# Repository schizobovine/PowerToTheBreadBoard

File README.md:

# PowerToTheBreadBoard
Variations of power supplies/regulators designed to be clamped on to a bread board.

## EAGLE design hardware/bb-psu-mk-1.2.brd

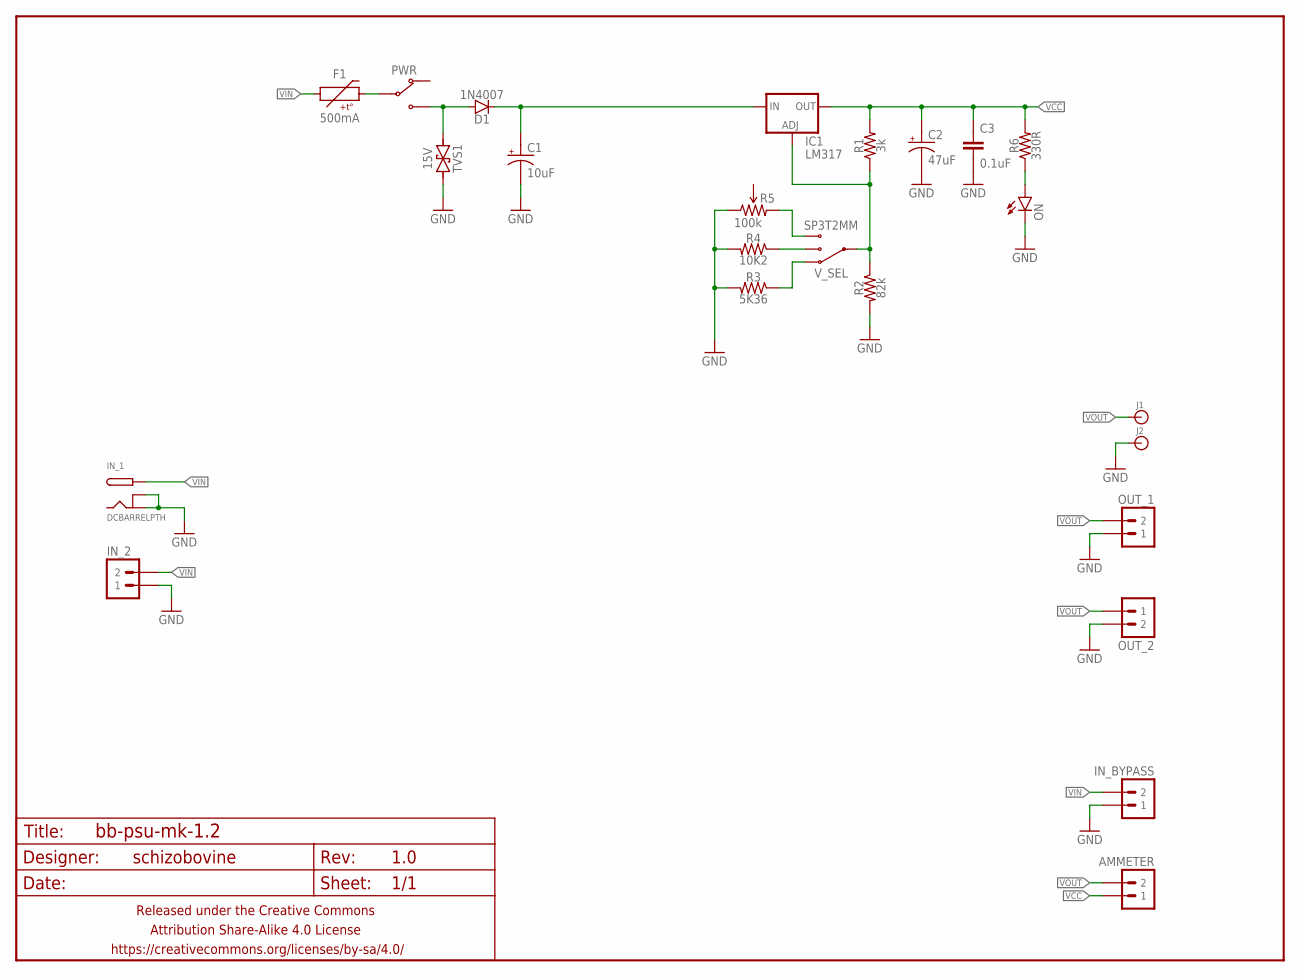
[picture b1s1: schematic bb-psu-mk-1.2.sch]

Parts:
AMMETER: M02PTH-CENTERED; 1X02-CENTER
C1: 10uF; E2,5-6
C2: 47uF; E2,5-6
C3: 0.1uF; C025-024X044
D1: 1N4007; DIODE-10.16MM
F1: 500mA; PTC-PTH-5.08MM
FRAME1: FRAME-LETTERNO_PACKAGE; DUMMY
IC1: LM317; TO220-THERMPAD
IN_1: DCBARRELPTH; DCJACK_2MM_PTH
IN_2: M02PTH-CENTERED-R+; 1X02-CENTER-R+
IN_BYPASS: M02PTH-CENTERED-R+; 1X02-CENTER-R+
J1, J2: BANANA_CONNPOAST; BINDING_POST
ON: LED3MM-LESS; LED3MM-LESSSILK
OUT_1: M02PTH-CENTERED-R+; 1X02-CENTER-R+
OUT_2: M023.5MM; SCREWTERMINAL-3.5MM-2
PWR: SWITCH-SPDTPTH-VERT-2.54MM; SWITCH-SPDT
R1: 3k; RESISTOR-AXIAL-PTH-7.62MM
R2: 82k; RESISTOR-AXIAL-PTH-7.62MM
R3: 5K36; RESISTOR-AXIAL-PTH-7.62MM
R4: 10K2; RESISTOR-AXIAL-PTH-7.62MM
R5: 100k; 3386U
R6: 330R; RESISTOR-AXIAL-PTH-6.35MM
TVS1: 15V; DO-41-TVS-BI-10.16MM
V_SEL: SP3T2MM; SP3T-2MM

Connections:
GND: C1.-, C2.-, C3.2, IN_1.BRK, IN_1.GND, IN_2.1, IN_BYPASS.1, J2.P$1, ON.K (C), OUT_1.1, OUT_2.2, R2.P$2 (2), R3.P$2 (2), R4.P$2 (2), R5.1 (CCW), TVS1.P$2 (2)
unnamed: D1.A, PWR.3 (NO), TVS1.P$1 (1)
unnamed: C1.+, D1.C, IC1.3 (IN)
unnamed: F1.P$2 (2), PWR.2 (COM)
unnamed: ON.A, R6.P$1 (1)
unnamed: R4.P$1 (1), V_SEL.P$3 (B)
unnamed: IC1.1 (ADJ), R1.P$1 (1), R2.P$1 (1), V_SEL.P$1 (COM)
unnamed: R3.P$1 (1), V_SEL.P$2 (A)
unnamed: R5.3 (CW), V_SEL.P$4 (C)
VCC: AMMETER.1, C2.+, C3.1, IC1.2@1 (OUT), IC1.2@2 (OUT), R1.P$2 (2), R6.P$2 (2)
VIN: F1.P$1 (1), IN_1.PWR, IN_2.2, IN_BYPASS.2
VOUT: AMMETER.2, J1.P$1, OUT_1.2, OUT_2.1

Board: 2 copper layers, 28 parts (2 on the bottom side), 12 nets, no tracks yet.

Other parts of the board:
U$1, U$2: CC-BY-SA-4.0-NO-URL
U$3: COW

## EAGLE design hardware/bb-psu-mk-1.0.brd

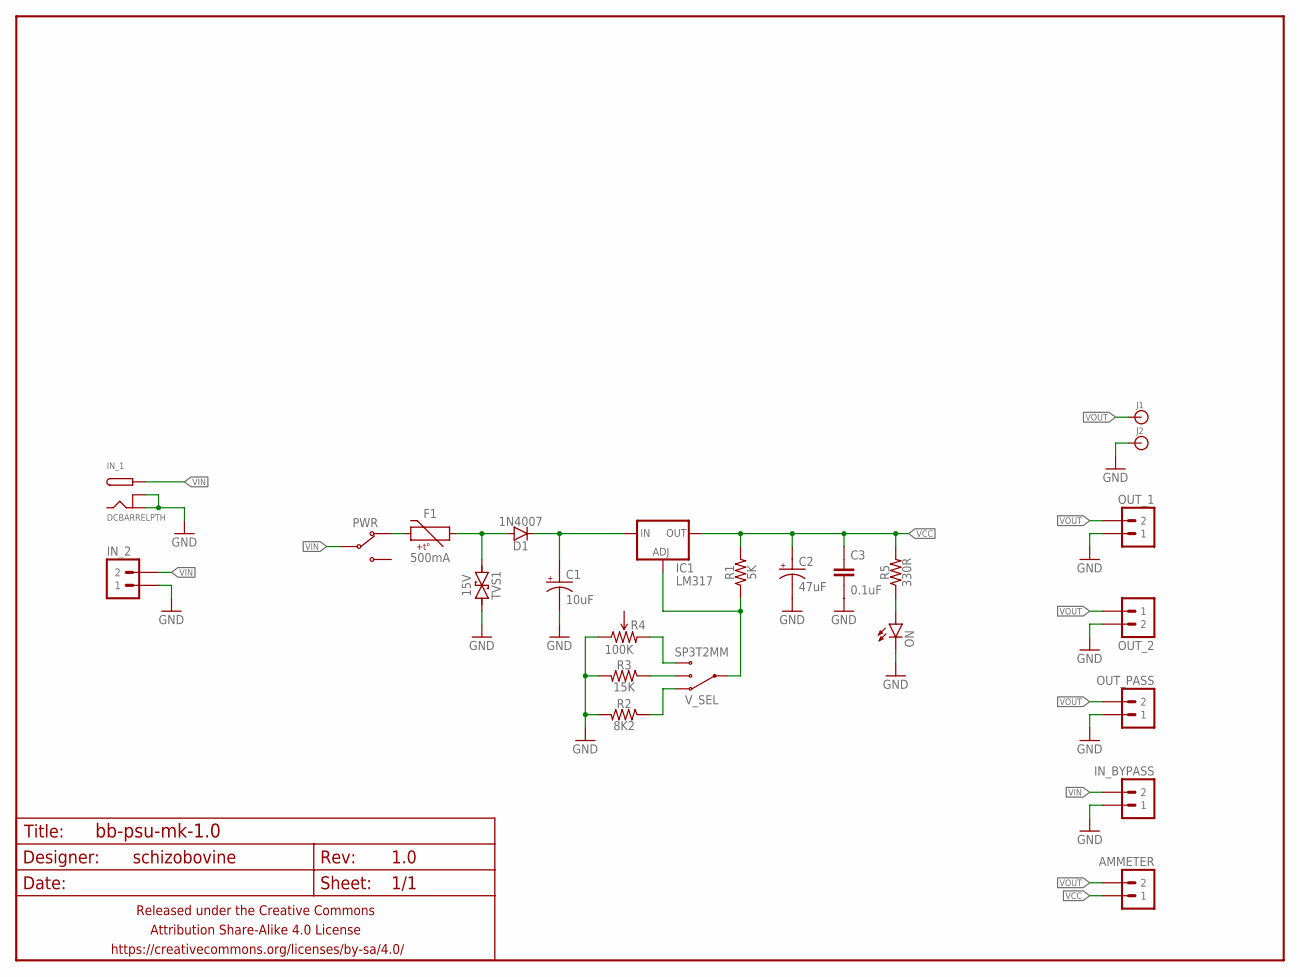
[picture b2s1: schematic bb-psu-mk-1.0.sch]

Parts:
AMMETER: M02PTH-CENTERED; 1X02-CENTER
C1: 10uF; E2,5-6
C2: 47uF; E2,5-6
C3: 0.1uF; C025-024X044
D1: 1N4007; DIODE-10.16MM
F1: 500mA; PTC-PTH-5.08MM
FRAME1: FRAME-LETTERNO_PACKAGE; DUMMY
IC1: LM317; TO220-THERMPAD
IN_1: DCBARRELPTH; DCJACK_2MM_PTH
IN_2: M02PTH-CENTERED-R+; 1X02-CENTER-R+
IN_BYPASS: M02PTH-CENTERED-R+; 1X02-CENTER-R+
J1, J2: BANANA_CONNPOAST; BINDING_POST
ON: LED3MM-LESS; LED3MM-LESSSILK
OUT_1: M02PTH-CENTERED-R+; 1X02-CENTER-R+
OUT_2: M023.5MM; SCREWTERMINAL-3.5MM-2
OUT_PASS: M02PTH-CENTERED-R+; 1X02-CENTER-R+
PWR: SWITCH-SPDTPTH-RA-2.54MM; SPDT-RA-2.54MM
R1: 5K; RESISTOR-AXIAL-PTH-6.35MM
R2: 8K2; RESISTOR-AXIAL-PTH-6.35MM
R3: 15K; RESISTOR-AXIAL-PTH-6.35MM
R4: 100K; 3386U
R5: 330R; RESISTOR-AXIAL-PTH-6.35MM
TVS1: 15V; DO-41-TVS-BI-10.16MM
V_SEL: SP3T2MM; SP3T-2MM

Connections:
GND: C1.-, C2.-, C3.2, IN_1.BRK, IN_1.GND, IN_2.1, IN_BYPASS.1, J2.P$1, ON.K (C), OUT_1.1, OUT_2.2, OUT_PASS.1, R2.P$2 (2), R3.P$2 (2), R4.1 (CCW), TVS1.P$2 (2)
unnamed: D1.A, F1.P$1 (1), TVS1.P$1 (1)
unnamed: C1.+, D1.C, IC1.3 (IN)
unnamed: F1.P$2 (2), PWR.1 (NC)
unnamed: ON.A, R5.P$1 (1)
unnamed: IC1.1 (ADJ), R1.P$1 (1), V_SEL.P$1 (COM)
unnamed: R3.P$1 (1), V_SEL.P$3 (B)
unnamed: R4.3 (CW), V_SEL.P$4 (C)
unnamed: R2.P$1 (1), V_SEL.P$2 (A)
VCC: AMMETER.1, C2.+, C3.1, IC1.2@1 (OUT), IC1.2@2 (OUT), R1.P$2 (2), R5.P$2 (2)
VIN: IN_1.PWR, IN_2.2, IN_BYPASS.2, PWR.2 (COM)
VOUT: AMMETER.2, J1.P$1, OUT_1.2, OUT_2.1, OUT_PASS.2

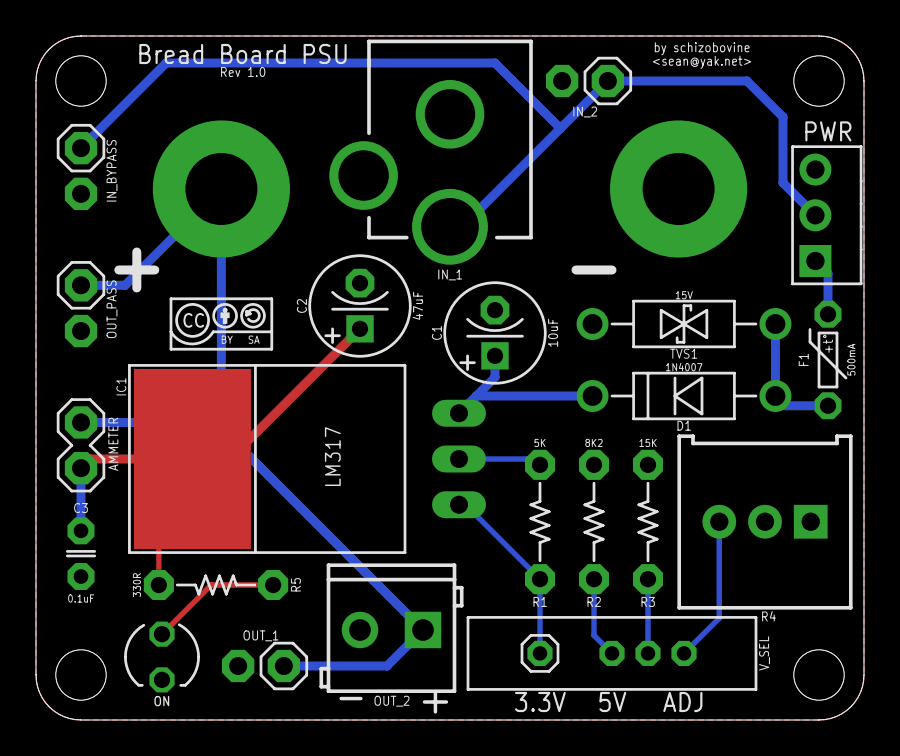
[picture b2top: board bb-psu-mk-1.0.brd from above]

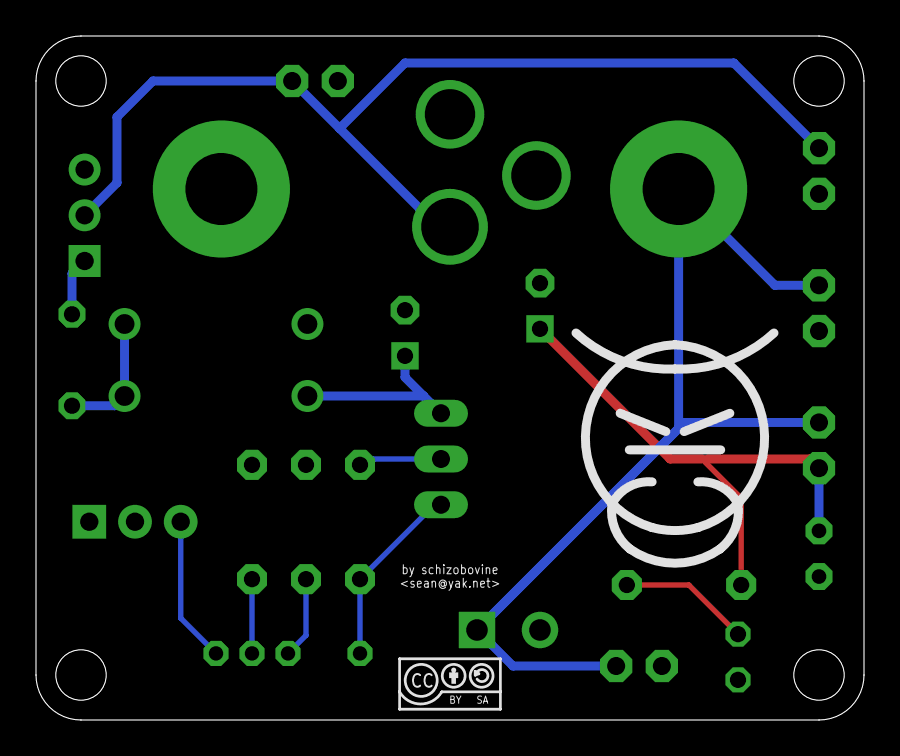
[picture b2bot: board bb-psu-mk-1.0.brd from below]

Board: 2 copper layers, 46.0 x 38.0 mm, 28 parts (2 on the bottom side), 12 nets.

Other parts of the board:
U$1, U$2: CC-BY-SA-4.0-NO-URL
U$3: COW

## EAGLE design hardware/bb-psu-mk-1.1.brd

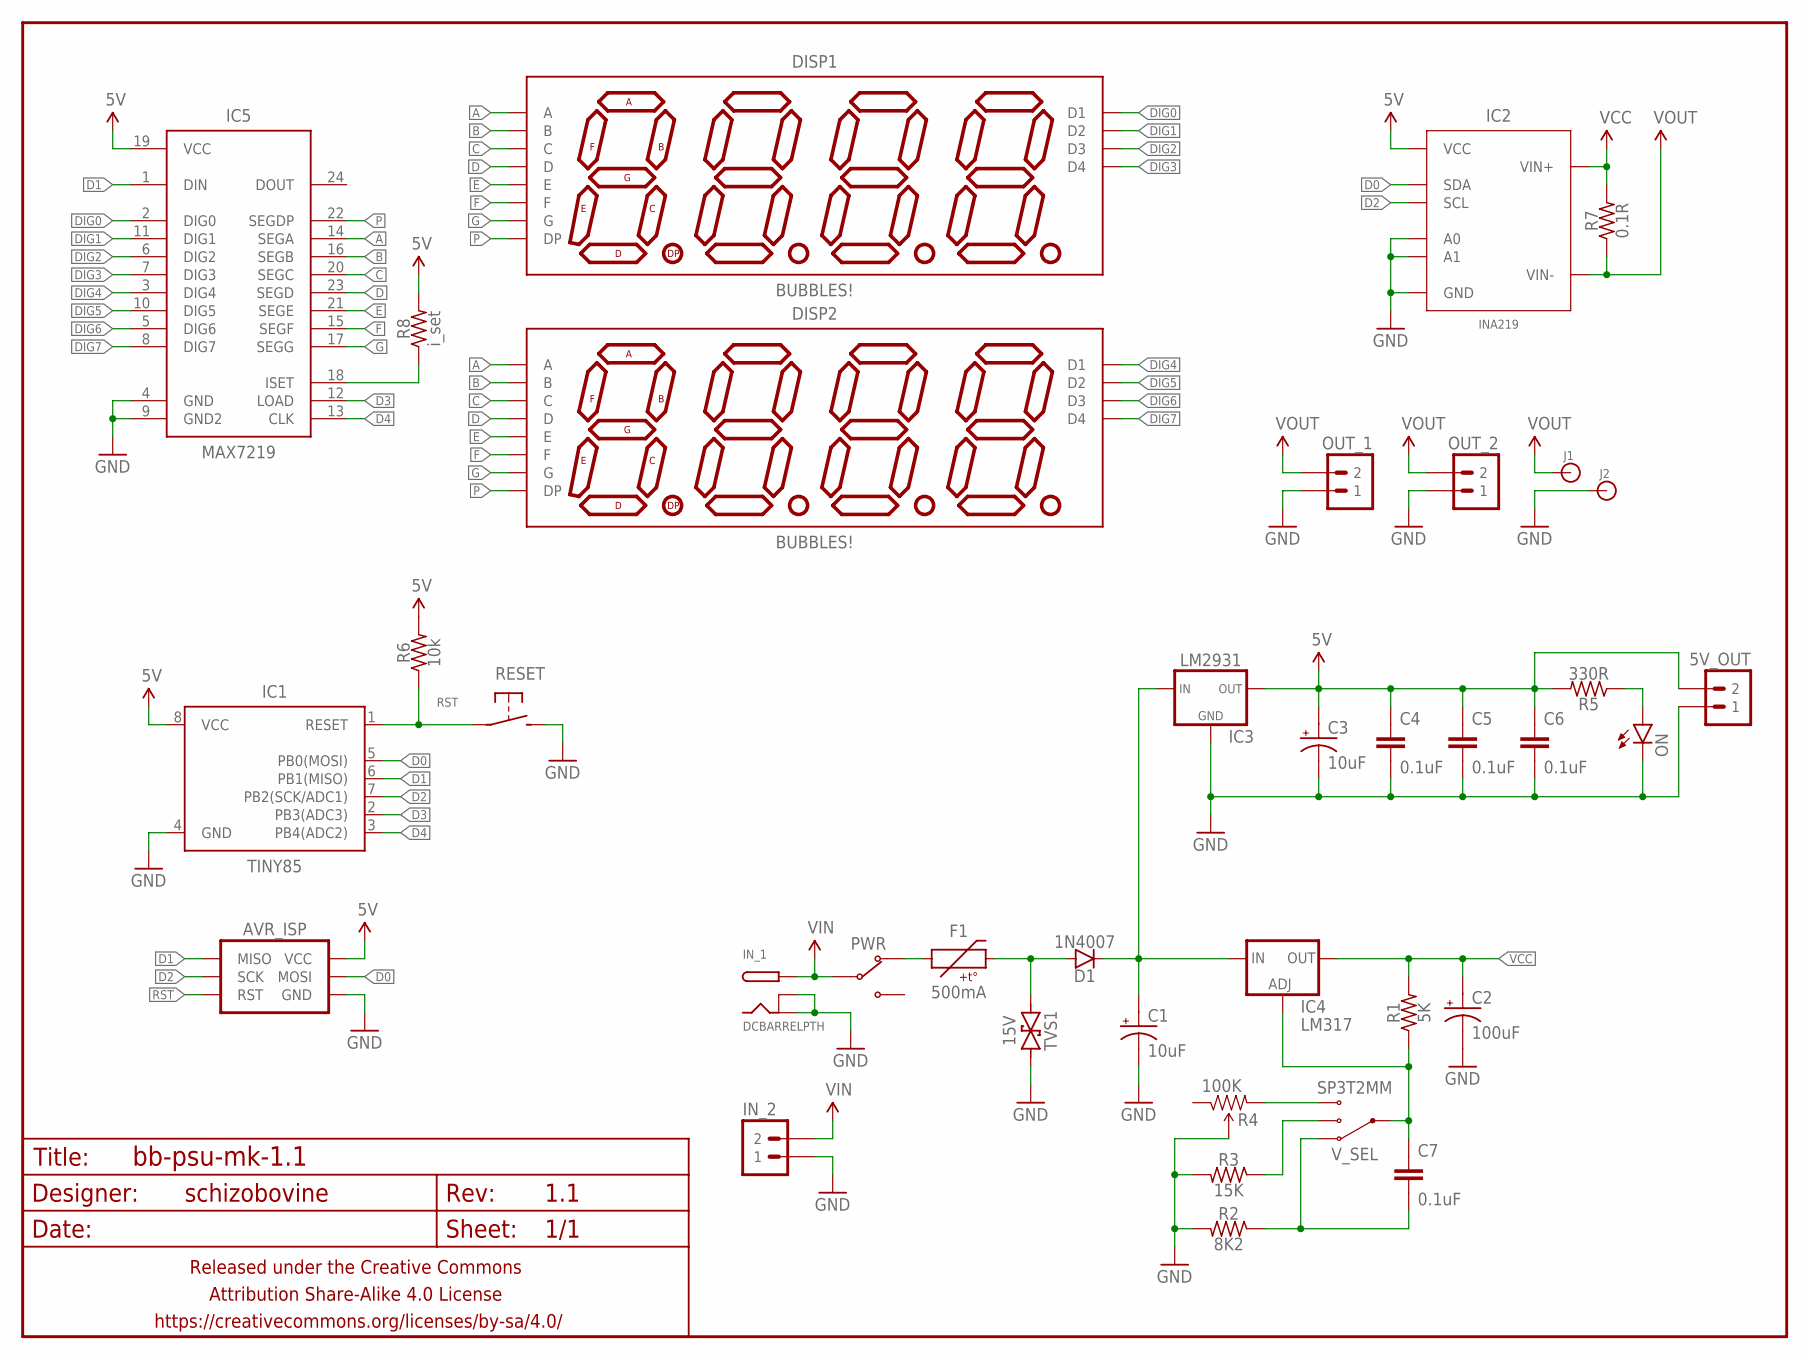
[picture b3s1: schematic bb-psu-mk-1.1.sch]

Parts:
5V_OUT: M02PTH-CENTERED-R+; 1X02-CENTER-R+
AVR_ISP: AVR_SPI_PRG_6PTH; 2X3
C1: 10uF; E2,5-6
C2: 100uF; E2,5-6
C3: 10uF; E2-5
C4, C5, C6, C7: 0.1uF; C025-024X044
D1: 1N4007; DIODE-10.16MM
DISP1, DISP2: BUBBLES!; DIL12
F1: 500mA; PTC-PTH-5.08MM
FRAME1: FRAME-LETTERNO_PACKAGE; DUMMY
IC1: TINY85; DIP08
IC2: INA219; SO08
IC3: LM2931; TO-92-AMMO
IC4: LM317; TO220-THERMPAD
IC5: MAX7219; SO24W
IN_1: DCBARRELPTH; DCJACK_2MM_PTH
IN_2: M02PTH-CENTERED-R+; 1X02-CENTER-R+
J1, J2: BANANA_CONNPOAST; BINDING_POST
ON: LED3MM-LESS; LED3MM-LESSSILK
OUT_1, OUT_2: M02PTH-CENTERED-R+; 1X02-CENTER-R+
PWR: SWITCH-SPDTPTH-VERT-2.54MM; SWITCH-SPDT
R1: 5K; RESISTOR-AXIAL-PTH-6.35MM
R2: 8K2; RESISTOR-AXIAL-PTH-6.35MM
R3: 15K; RESISTOR-AXIAL-PTH-6.35MM
R4: 100K; 3386U
R5: 330R; RESISTOR-AXIAL-PTH-5.08MM
R6: 10k; RESISTOR-AXIAL-PTH-5.08MM
R7: 0.1R; RESISTOR-AXIAL-PTH-10.16MM
R8: i_set; RESISTOR-AXIAL-PTH-5.08MM
RESET: SPST-NO-TACT3MM-PTH-SMALL-PADS; DTS-3-SMALL-PADS
TVS1: 15V; DO-41-TVS-BI-10.16MM
V_SEL: SP3T2MM; SP3T-2MM

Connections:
5V: 5V_OUT.2, AVR_ISP.2 (VCC), C3.+, C4.1, C5.1, C6.1, IC1.8 (VCC), IC2.5 (VCC), IC3.3 (OUT), IC5.19 (VCC), R5.P$2 (2), R6.P$2 (2), R8.P$2 (2)
A: DISP1.12 (A), DISP2.12 (A), IC5.14 (SEGA)
B: DISP1.11 (B), DISP2.11 (B), IC5.16 (SEGB)
C: DISP1.3 (C), DISP2.3 (C), IC5.20 (SEGC)
D: DISP1.8 (D), DISP2.8 (D), IC5.23 (SEGD)
D0: AVR_ISP.4 (MOSI), IC1.5 (PB0(MOSI)), IC2.3 (SDA)
D1: AVR_ISP.1 (MISO), IC1.6 (PB1(MISO)), IC5.1 (DIN)
D2: AVR_ISP.3 (SCK), IC1.7 (PB2(SCK/ADC1)), IC2.4 (SCL)
D3: IC1.2 (PB3(ADC3)), IC5.12 (LOAD)
D4: IC1.3 (PB4(ADC2)), IC5.13 (CLK)
DIG0: DISP1.1 (D1), IC5.2 (DIG0)
DIG1: DISP1.10 (D2), IC5.11 (DIG1)
DIG2: DISP1.4 (D3), IC5.6 (DIG2)
DIG3: DISP1.6 (D4), IC5.7 (DIG3)
DIG4: DISP2.1 (D1), IC5.3 (DIG4)
DIG5: DISP2.10 (D2), IC5.10 (DIG5)
DIG6: DISP2.4 (D3), IC5.5 (DIG6)
DIG7: DISP2.6 (D4), IC5.8 (DIG7)
E: DISP1.2 (E), DISP2.2 (E), IC5.21 (SEGE)
F: DISP1.9 (F), DISP2.9 (F), IC5.15 (SEGF)
G: DISP1.7 (G), DISP2.7 (G), IC5.17 (SEGG)
GND: 5V_OUT.1, AVR_ISP.6 (GND), C1.-, C2.-, C3.-, C4.2, C5.2, C6.2, IC1.4 (GND), IC2.1 (A1), IC2.2 (A0), IC2.6 (GND), IC3.2 (GND), IC5.4 (GND), IC5.9 (GND2), IN_1.BRK, IN_1.GND, IN_2.1, J2.P$1, ON.K (C), OUT_1.1, OUT_2.1, R2.P$2 (2), R3.P$2 (2), R4.2 (WIPER), RESET.2, TVS1.P$2 (2)
unnamed: D1.A, F1.P$2 (2), TVS1.P$1 (1)
unnamed: C1.+, D1.C, IC3.1 (IN), IC4.3 (IN)
unnamed: F1.P$1 (1), PWR.1 (NC)
unnamed: ON.A, R5.P$1 (1)
unnamed: IC5.18 (ISET), R8.P$1 (1)
unnamed: C7.1, IC4.1 (ADJ), R1.P$1 (1), V_SEL.P$1 (COM)
unnamed: R3.P$1 (1), V_SEL.P$3 (B)
unnamed: R4.3 (CW), V_SEL.P$4 (C)
unnamed: C7.2, R2.P$1 (1), V_SEL.P$2 (A)
P: DISP1.5 (DP), DISP2.5 (DP), IC5.22 (SEGDP)
RST: AVR_ISP.5 (RST), IC1.1 (RESET), R6.P$1 (1), RESET.1
VCC: C2.+, IC2.8 (VIN+), IC4.2@1 (OUT), IC4.2@2 (OUT), R1.P$2 (2), R7.P$2 (2)
VIN: IN_1.PWR, IN_2.2, PWR.2 (COM)
VOUT: IC2.7 (VIN-), J1.P$1, OUT_1.2, OUT_2.2, R7.P$1 (1)

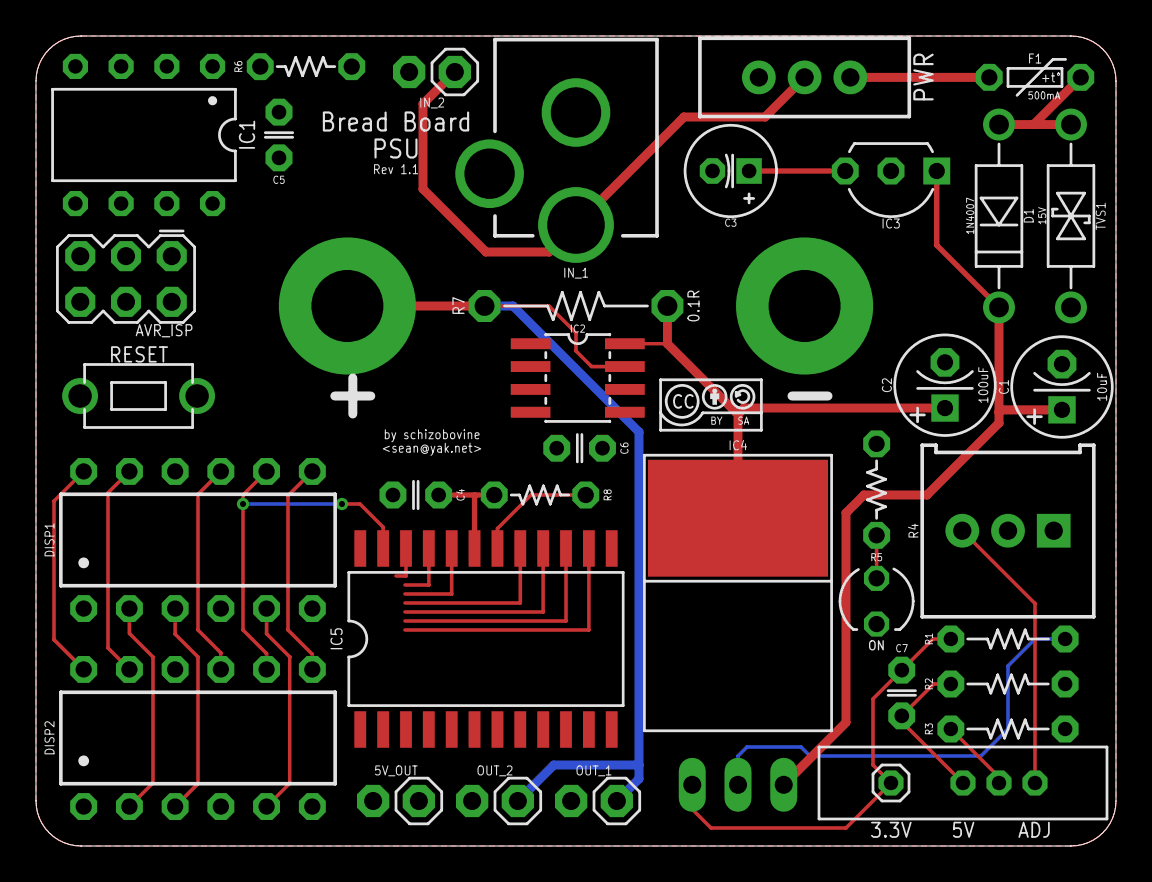
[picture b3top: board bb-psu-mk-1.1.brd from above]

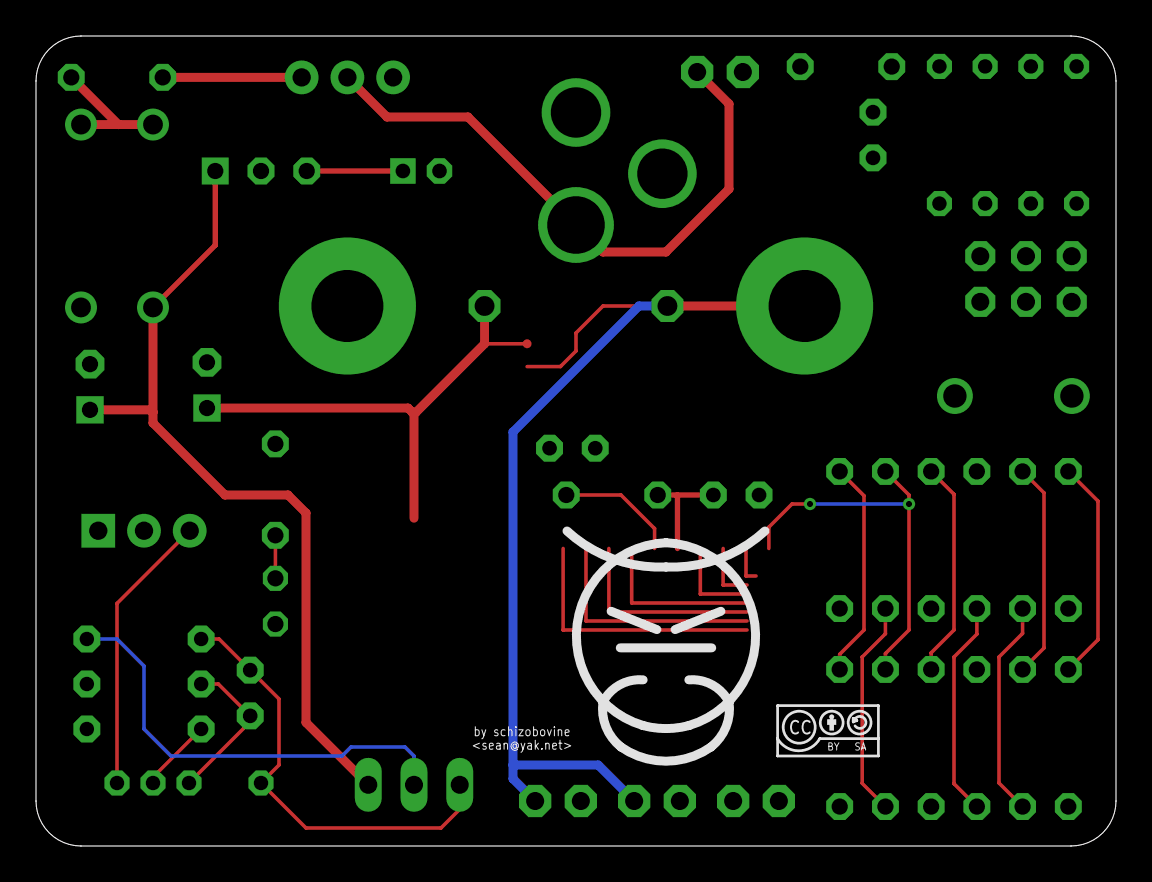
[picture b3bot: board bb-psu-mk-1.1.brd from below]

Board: 2 copper layers, 60.0 x 45.0 mm, 41 parts (2 on the bottom side), 36 nets.

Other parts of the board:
U$1, U$2: CC-BY-SA-4.0-NO-URL
U$3: COW

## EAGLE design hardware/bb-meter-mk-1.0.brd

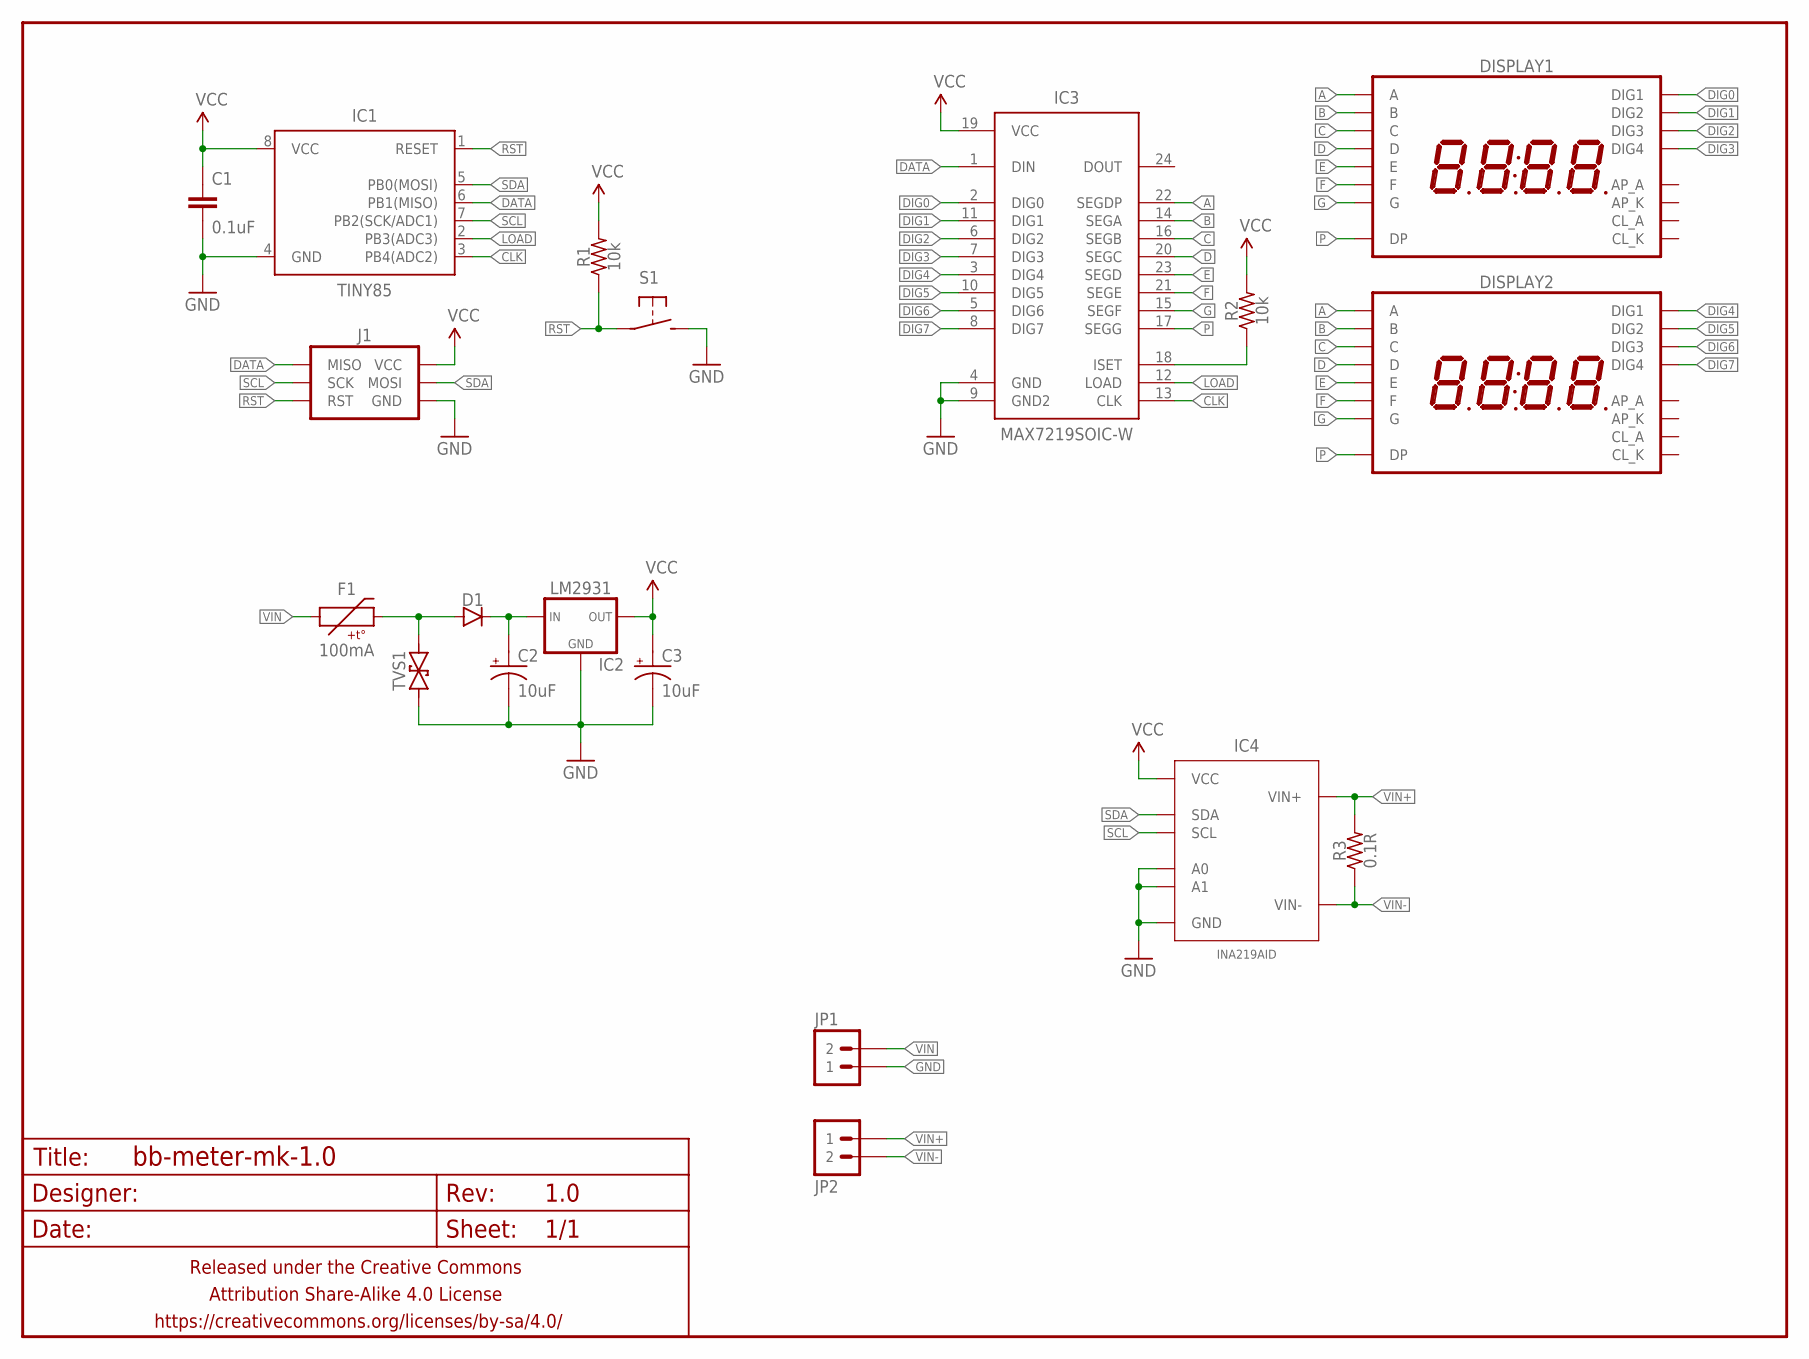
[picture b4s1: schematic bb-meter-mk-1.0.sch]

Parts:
C1: 0.1uF; C025-024X044
C2, C3: 10uF; E2,5-5
D1: DIODEPTH-10.68MM; DIODE-10.16MM
DISPLAY1, DISPLAY2: 7SEG_4DIGIT_COLON_APOS; 7SEG_4DIG_10MM
F1: 100mA; PTC-PTH-5.08MM
FRAME1: FRAME-LETTERNO_PACKAGE; DUMMY
IC1: TINY85; DIP08
IC2: LM2931; TO-92-AMMO
IC3: MAX7219SOIC-W; SO24W
IC4: INA219AID; SO08
J1: AVR_SPI_PRG_6PTH; 2X3
JP1: M02PTH-CENTERED-R+; 1X02-CENTER-R+
JP2: M02PTH-CENTERED; 1X02-CENTER
R1: 10k; RESISTOR-AXIAL-PTH-6.35MM
R2: 10k; R0805
R3: 0.1R; RESISTOR-AXIAL-PTH-10.16MM
S1: SPST-NO-TACT6MM-PTH-SMALL-PADS; DTS-6-SMALL-PADS
TVS1: TVSDO-41-10.16MM; DO-41-TVS-BI-10.16MM

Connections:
A: DISPLAY1.14 (A), DISPLAY2.14 (A), IC3.22 (SEGDP)
B: DISPLAY1.16 (B), DISPLAY2.16 (B), IC3.14 (SEGA)
C: DISPLAY1.13 (C), DISPLAY2.13 (C), IC3.16 (SEGB)
CLK: IC1.3 (PB4(ADC2)), IC3.13 (CLK)
D: DISPLAY1.3 (D), DISPLAY2.3 (D), IC3.20 (SEGC)
DATA: IC1.6 (PB1(MISO)), IC3.1 (DIN), J1.1 (MISO)
DIG0: DISPLAY1.1 (DIG1), IC3.2 (DIG0)
DIG1: DISPLAY1.2 (DIG2), IC3.11 (DIG1)
DIG2: DISPLAY1.6 (DIG3), IC3.6 (DIG2)
DIG3: DISPLAY1.8 (DIG4), IC3.7 (DIG3)
DIG4: DISPLAY2.1 (DIG1), IC3.3 (DIG4)
DIG5: DISPLAY2.2 (DIG2), IC3.10 (DIG5)
DIG6: DISPLAY2.6 (DIG3), IC3.5 (DIG6)
DIG7: DISPLAY2.8 (DIG4), IC3.8 (DIG7)
E: DISPLAY1.5 (E), DISPLAY2.5 (E), IC3.23 (SEGD)
F: DISPLAY1.11 (F), DISPLAY2.11 (F), IC3.21 (SEGE)
G: DISPLAY1.15 (G), DISPLAY2.15 (G), IC3.15 (SEGF)
GND: C1.2, C2.-, C3.-, IC1.4 (GND), IC2.2 (GND), IC3.4 (GND), IC3.9 (GND2), IC4.1 (A1), IC4.2 (A0), IC4.6 (GND), J1.6 (GND), JP1.1, S1.3 (2), S1.4 (2), TVS1.P$1 (1)
LOAD: IC1.2 (PB3(ADC3)), IC3.12 (LOAD)
unnamed: IC3.18 (ISET), R2.1
unnamed: D1.A, F1.P$2 (2), TVS1.P$2 (2)
unnamed: C2.+, D1.C, IC2.1 (IN)
P: DISPLAY1.7 (DP), DISPLAY2.7 (DP), IC3.17 (SEGG)
RST: IC1.1 (RESET), J1.5 (RST), R1.P$1 (1), S1.1, S1.2 (1)
SCL: IC1.7 (PB2(SCK/ADC1)), IC4.4 (SCL), J1.3 (SCK)
SDA: IC1.5 (PB0(MOSI)), IC4.3 (SDA), J1.4 (MOSI)
VCC: C1.1, C3.+, IC1.8 (VCC), IC2.3 (OUT), IC3.19 (VCC), IC4.5 (VCC), J1.2 (VCC), R1.P$2 (2), R2.2
VIN: F1.P$1 (1), JP1.2
VIN+: IC4.8 (VIN+), JP2.1, R3.P$2 (2)
VIN-: IC4.7 (VIN-), JP2.2, R3.P$1 (1)

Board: 2 copper layers, 20 parts (3 on the bottom side), 30 nets, no tracks yet.

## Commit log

2015-04-16 licensing and ignore filters
2015-04-16 initial commit of designs so far

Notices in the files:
parts and their libraries:
A_butts: Released under the Creative Commons Attribution Share-Alike 4.0 License
A_butts: https://creativecommons.org/licenses/by-sa/4.0
A_butts: Released under the Creative Commons
